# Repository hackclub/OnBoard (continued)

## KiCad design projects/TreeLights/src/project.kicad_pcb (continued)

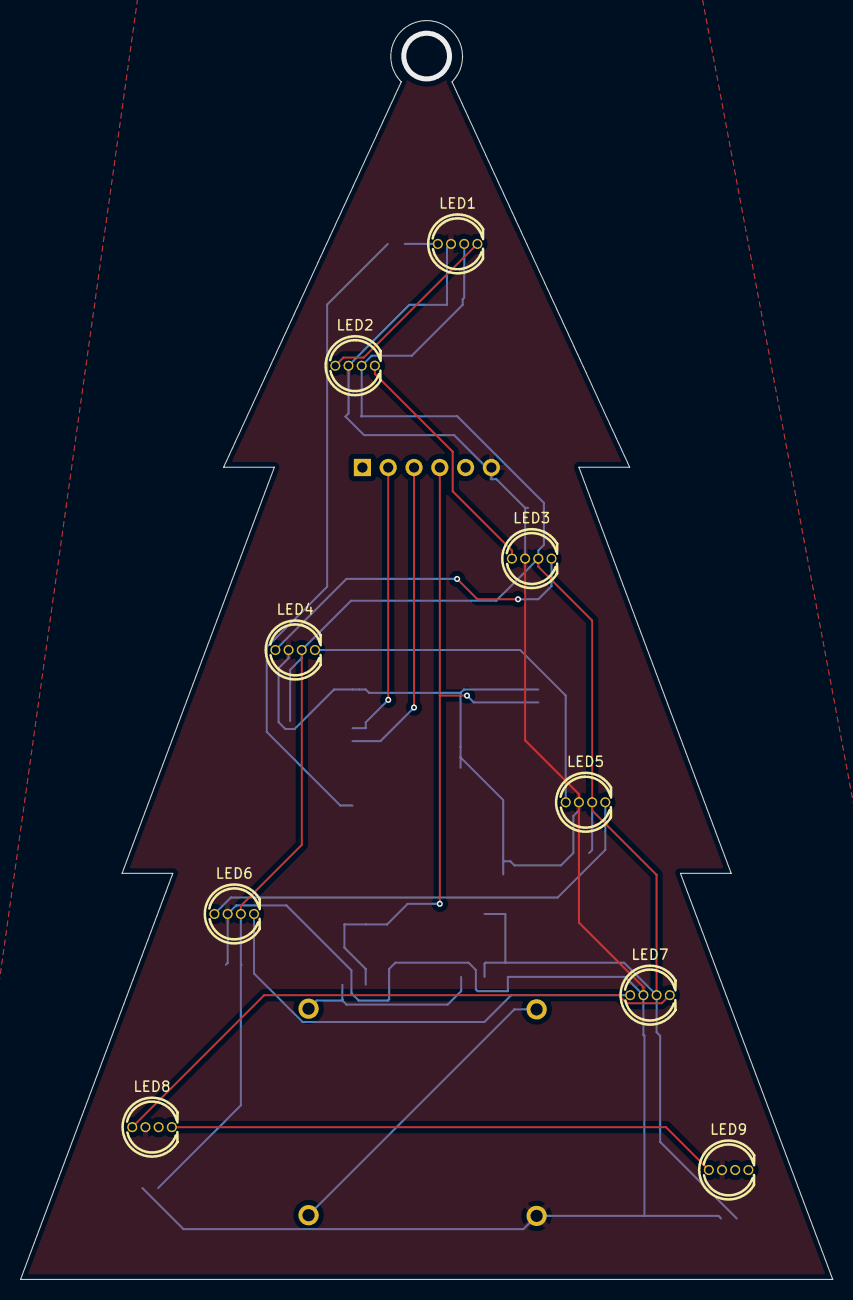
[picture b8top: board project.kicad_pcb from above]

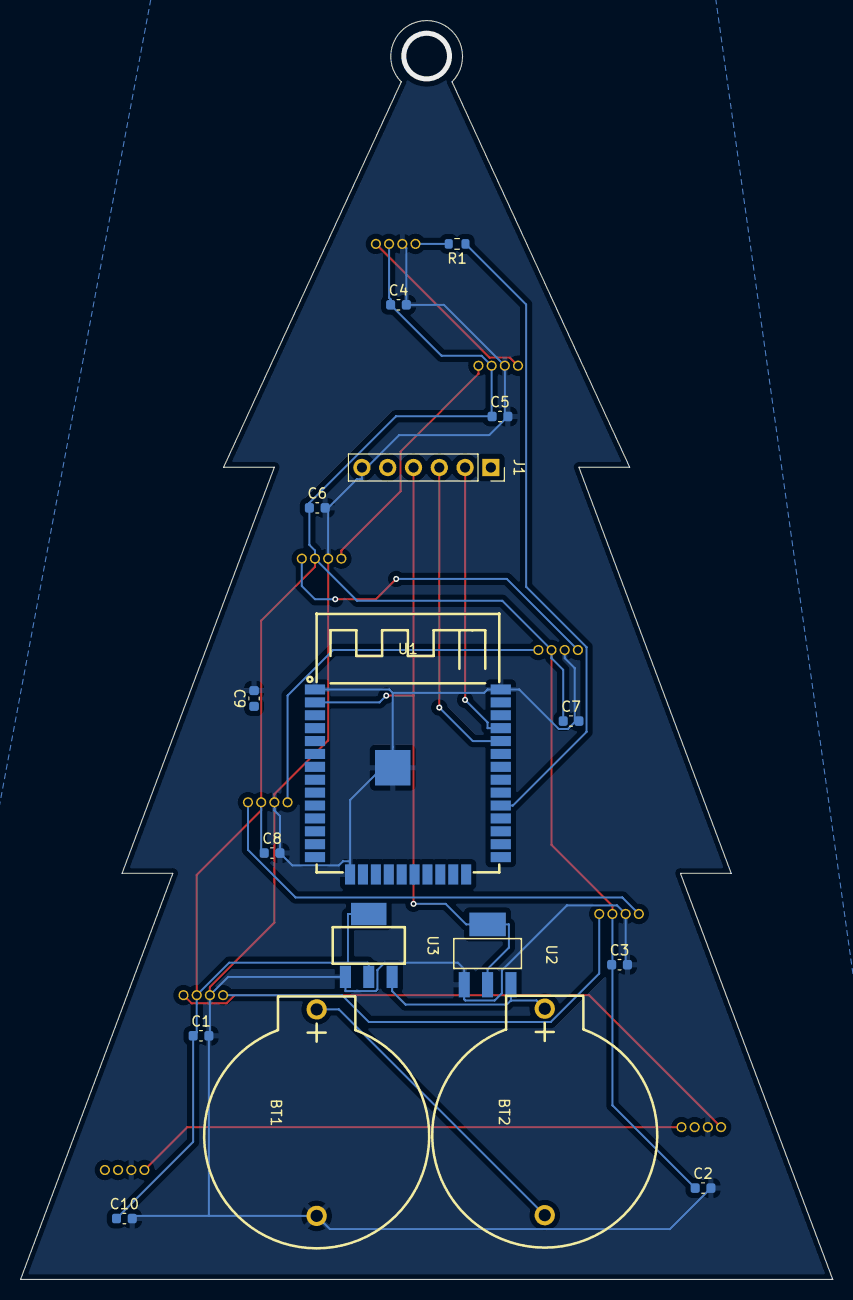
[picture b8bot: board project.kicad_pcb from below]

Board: 2 copper layers, 80.0 x 124.0 mm, 26 parts (17 on the bottom side), 17 nets.
